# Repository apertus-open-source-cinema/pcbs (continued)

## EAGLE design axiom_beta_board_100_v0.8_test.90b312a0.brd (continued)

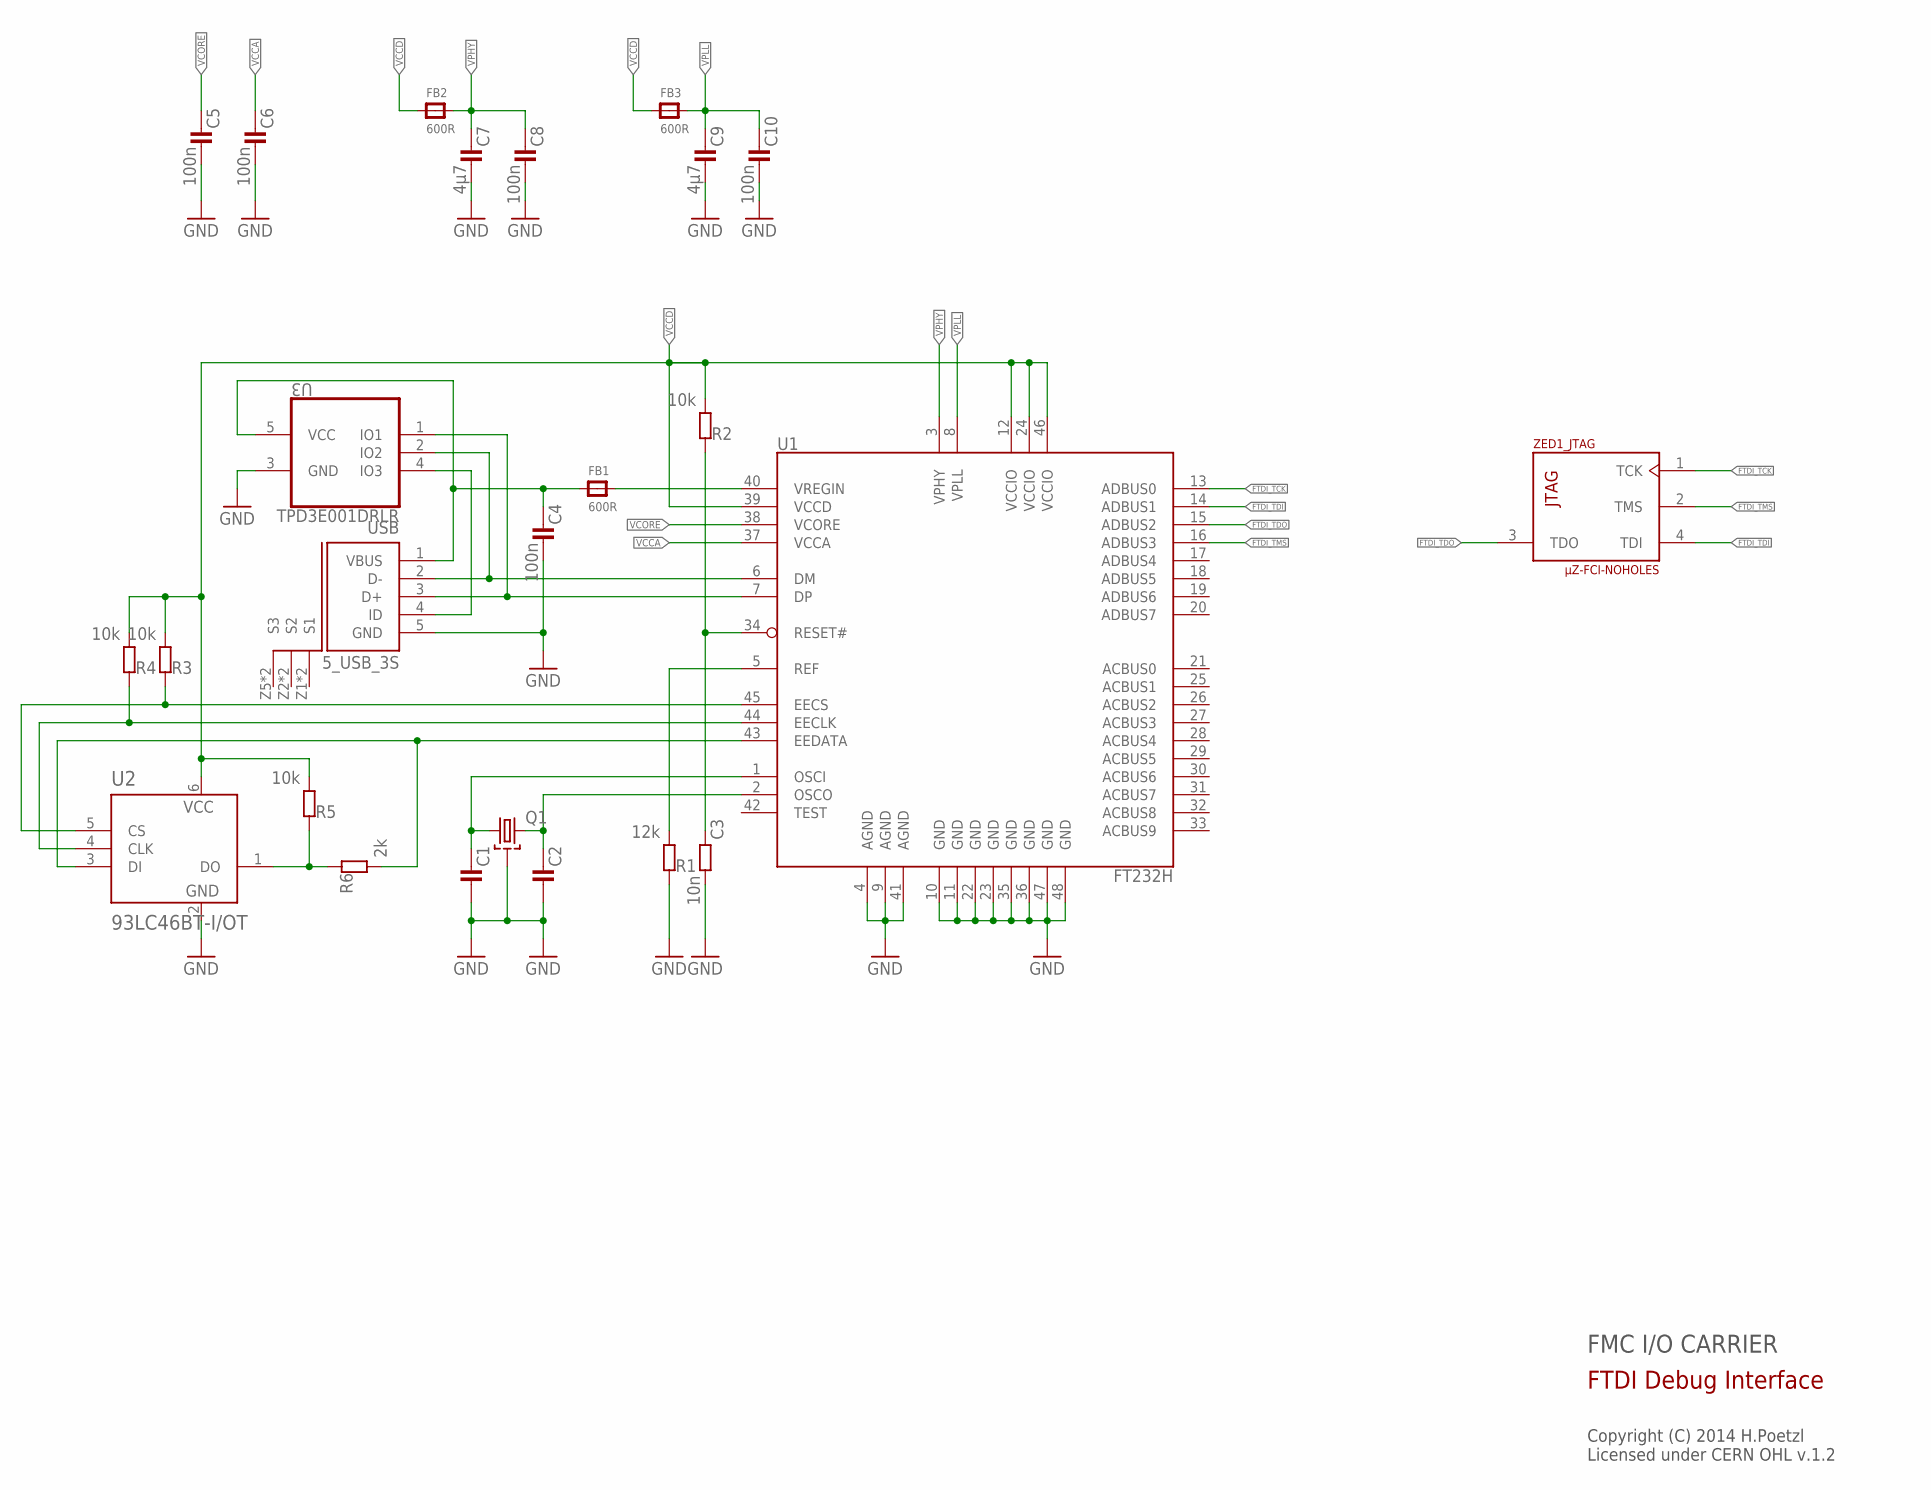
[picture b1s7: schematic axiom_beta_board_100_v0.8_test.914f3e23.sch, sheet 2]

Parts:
C1, C2: C0402-B; 0402-B
C3: 10n; 0402-B
C4: 100n; 0603-B
C5, C6, C8, C10: 100n; 0402-B
C7, C9: 4µ7; 0603-B
FB1, FB2, FB3: 600R; _0603MP
Q1: SMD-4P-2G-3.2X2.5; ABM8G
R1: 12k; 0402-B
R2, R3, R4, R5: 10k; 0402-B
R6: 2k; 0402-B
U1: FT232H; LQFP48
U2: 93LC46BT-I/OT; SOT95P280X145-6N
U3: TPD3E001DRLR; SOT50P160X60-5N
USB: 5_USB_3S; MICRO-AB-H-SMT
ZED1: µZ-FCI-NOHOLES; µZ-NOHOLES

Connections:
EE_CLK1: R4.1, U1.44 (EECLK), U2.4 (CLK)
EE_CS1: R3.1, U1.45 (EECS), U2.5 (CS)
EE_DATA1: R6.2, U1.43 (EEDATA), U2.3 (DI)
FTDI_D_N: U1.6 (DM), U3.2 (IO2), USB.2 (D-)
FTDI_D_P: U1.7 (DP), U3.1 (IO1), USB.3 (D+)
FTDI_TCK: U1.13 (ADBUS0), ZED1.1 (TCK)
FTDI_TDI: U1.14 (ADBUS1), ZED1.4 (TDI)
FTDI_TDO: U1.15 (ADBUS2), ZED1.3 (TDO)
FTDI_TMS: U1.16 (ADBUS3), ZED1.2 (TMS)
unnamed: R5.1, R6.1, U2.1 (DO)
unnamed: C1.1, Q1.1, U1.1 (OSCI)
unnamed: C2.1, Q1.3 (2), U1.2 (OSCO)
unnamed: C3.1, R2.1, U1.34 (RESET#)
unnamed: R1.2, U1.5 (REF)
unnamed: U3.4 (IO3), USB.4 (ID)
VBUS: C4.1, FB1.1, U3.5 (VCC), USB.1 (VBUS)
VCCA: C6.1, U1.37 (VCCA)
VCCD: FB2.1, FB3.1, R2.2, R3.2, R4.2, R5.2, U1.12 (VCCIO), U1.24 (VCCIO), U1.39 (VCCD), U1.46 (VCCIO), U2.6 (VCC)
VCORE: C5.1, U1.38 (VCORE)
VPHY: C7.1, C8.1, FB2.2, U1.3 (VPHY)
VPLL: C9.1, C10.1, FB3.2, U1.8 (VPLL)
VREGIN: FB1.2, U1.40 (VREGIN)

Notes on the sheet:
FMC I/O CARRIER
Copyright (C) 2014 H.Poetzl Licensed under CERN OHL v.1.2
FTDI Debug Interface

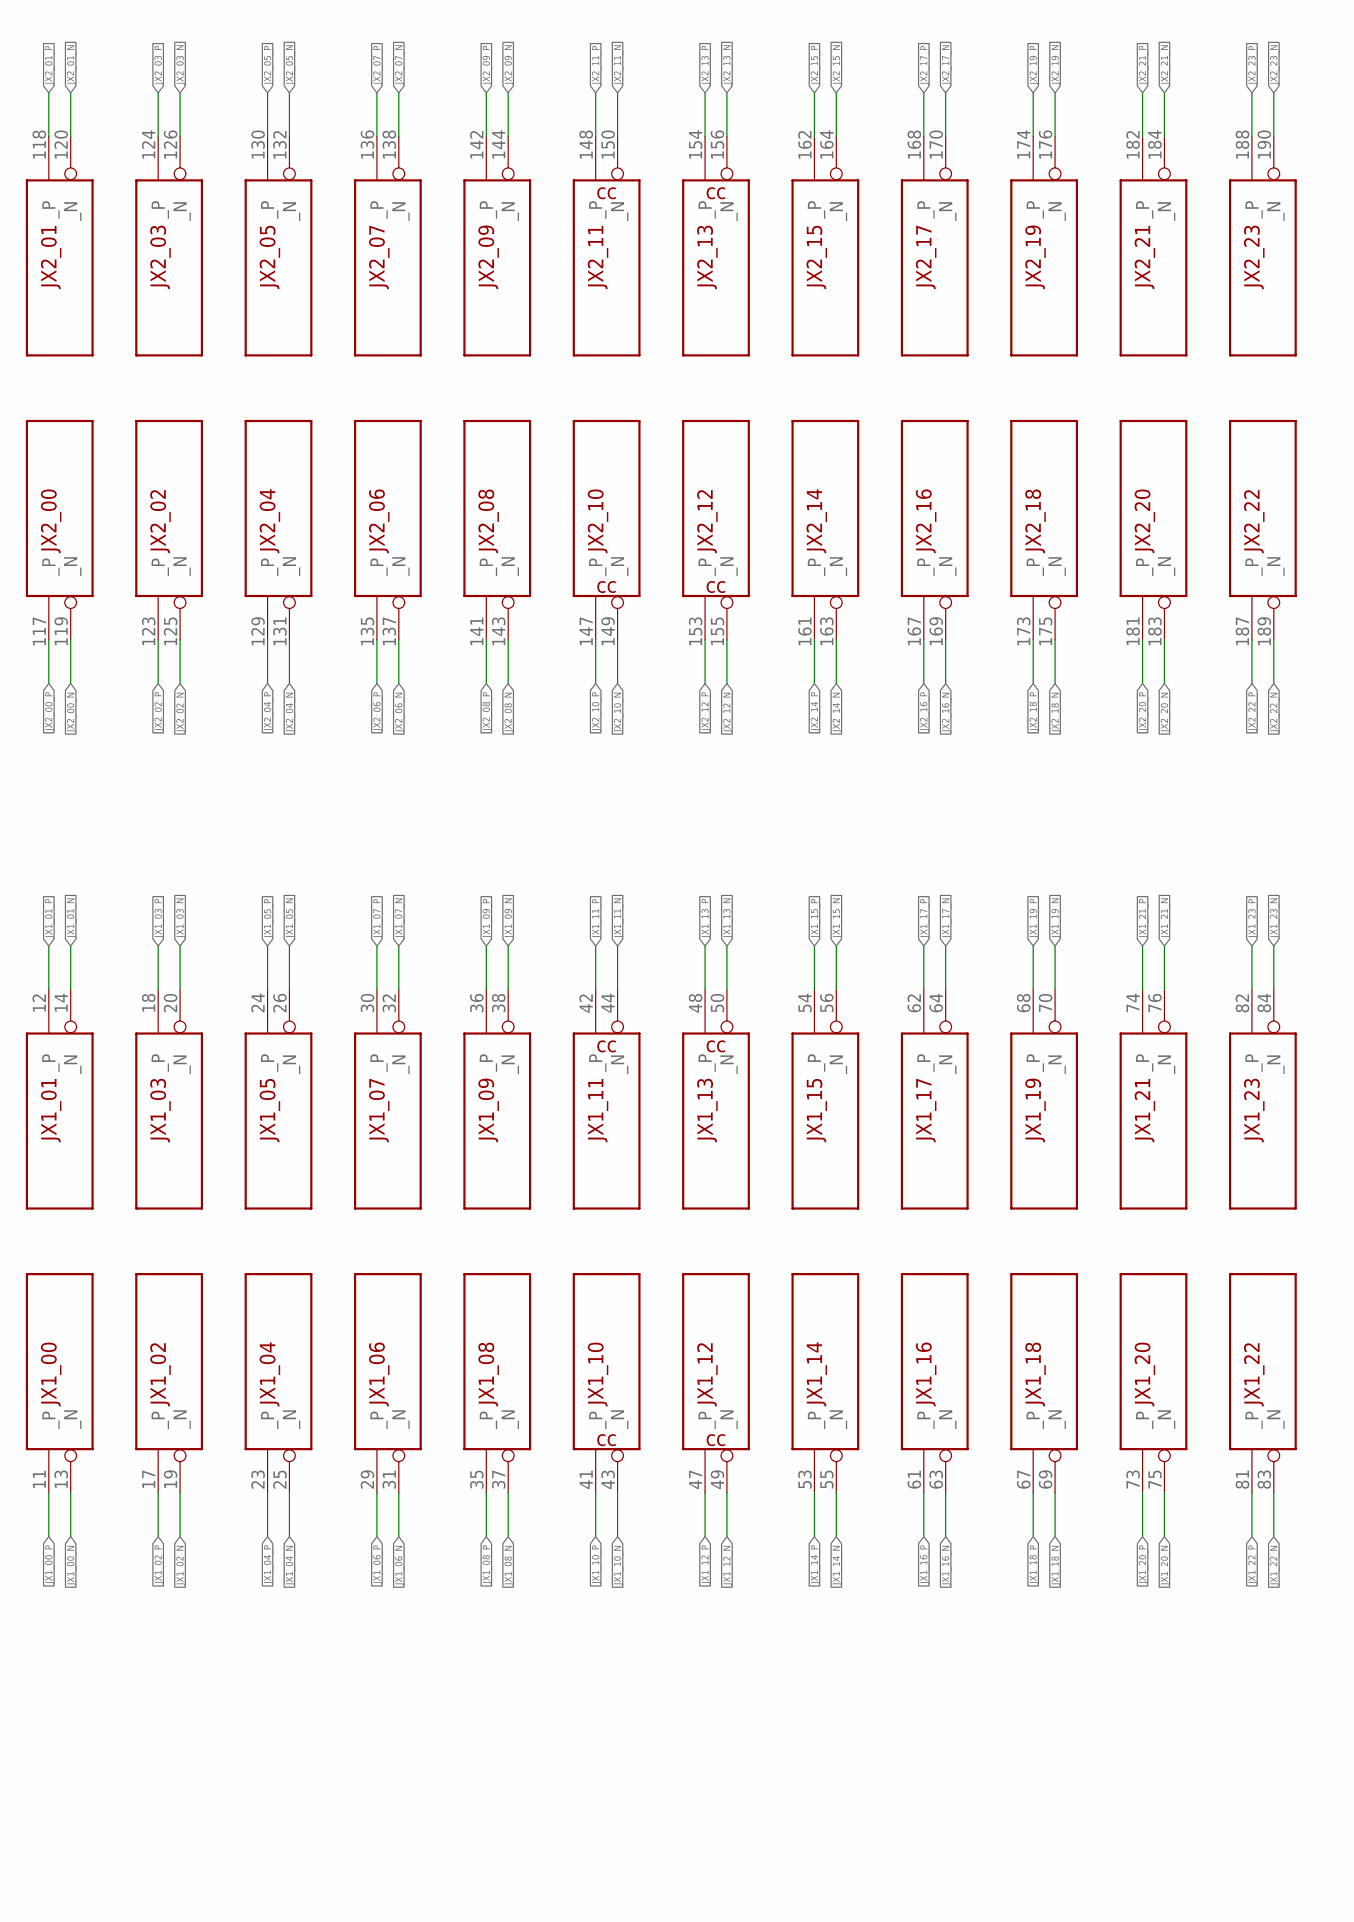
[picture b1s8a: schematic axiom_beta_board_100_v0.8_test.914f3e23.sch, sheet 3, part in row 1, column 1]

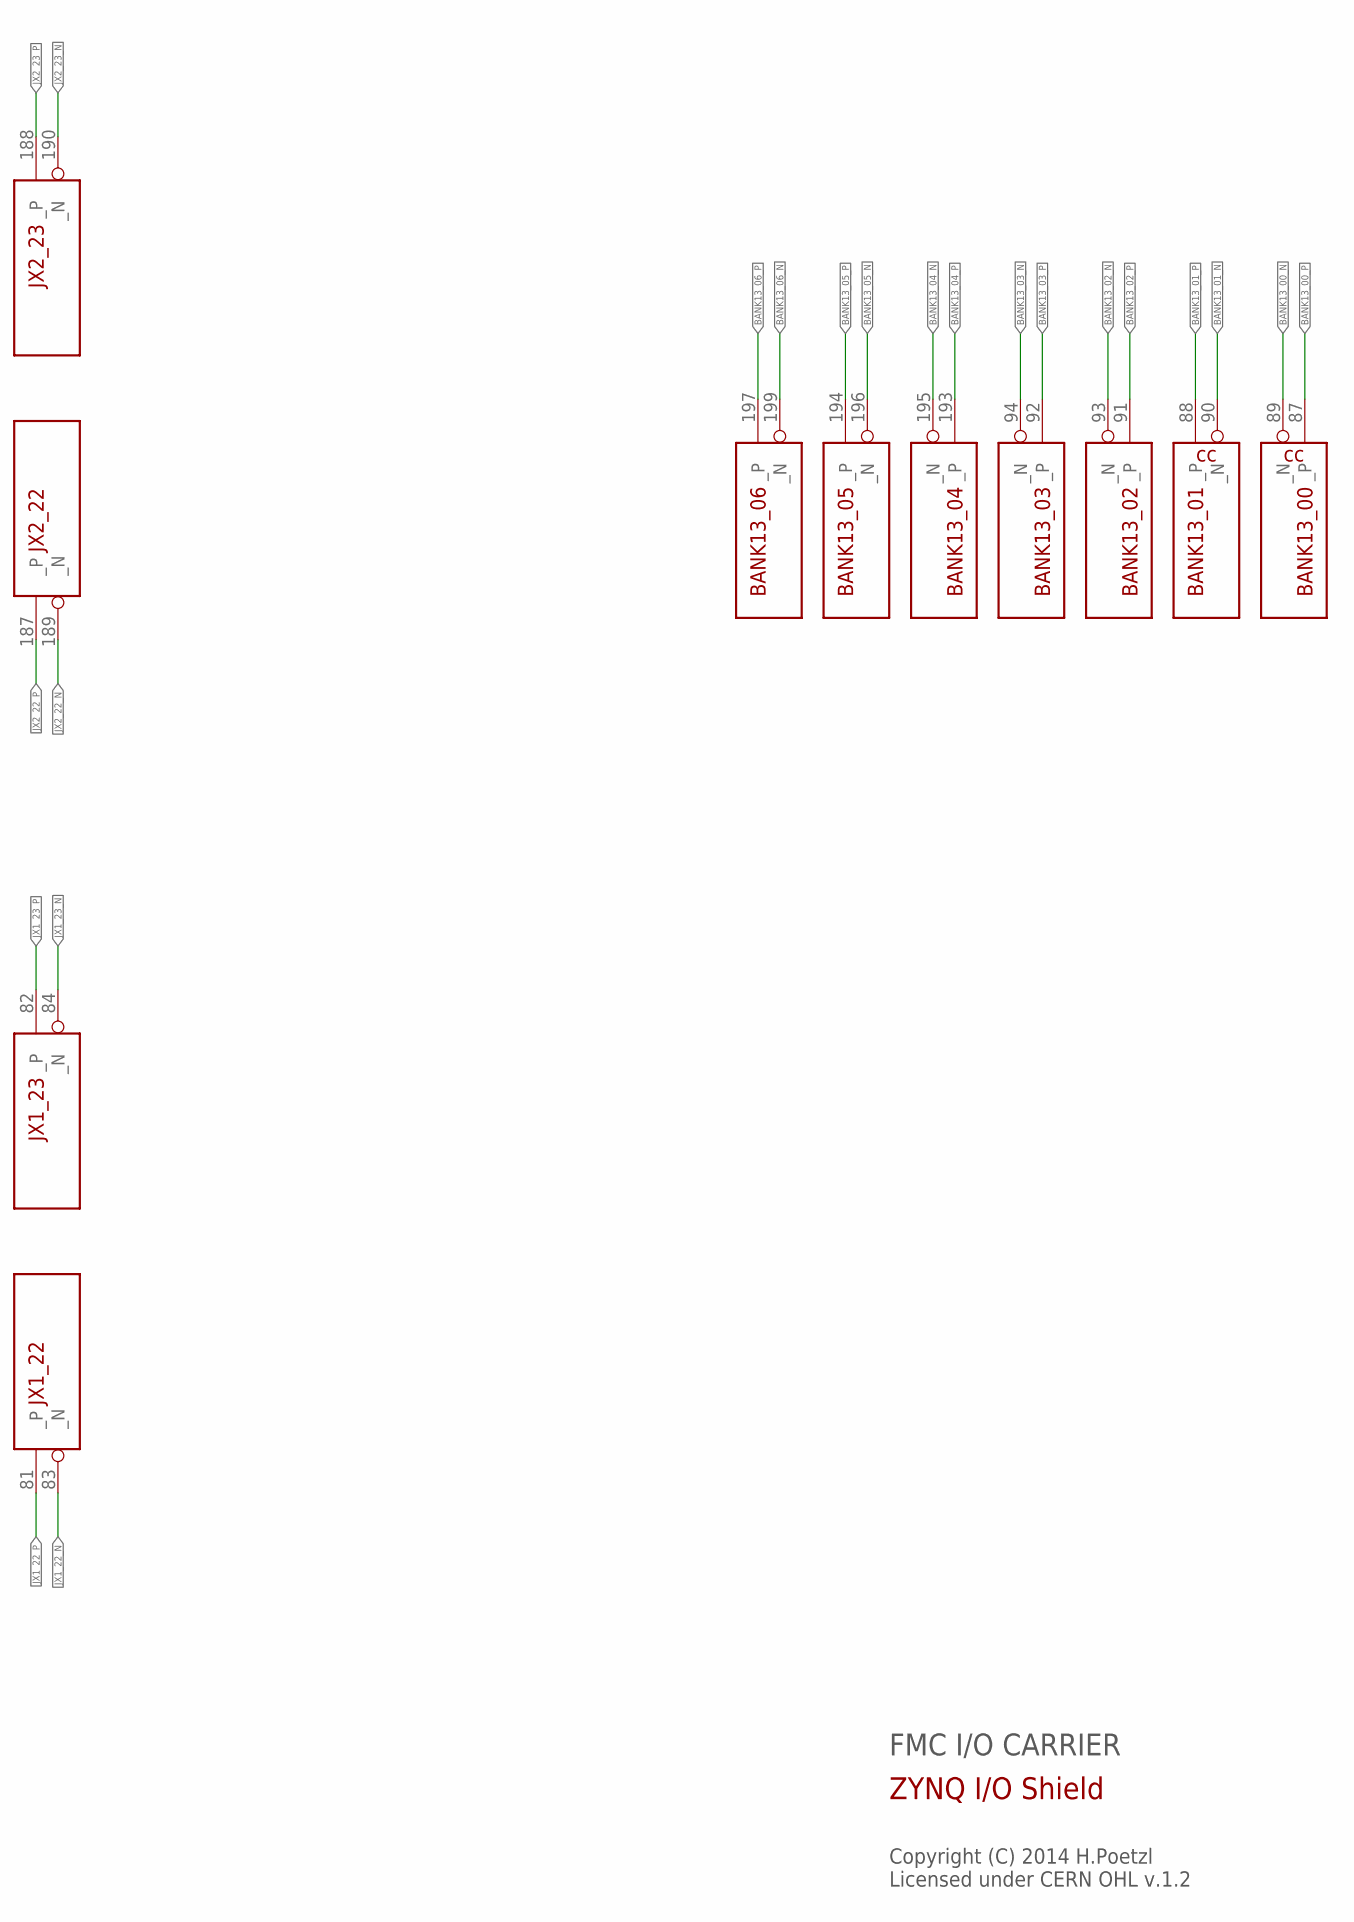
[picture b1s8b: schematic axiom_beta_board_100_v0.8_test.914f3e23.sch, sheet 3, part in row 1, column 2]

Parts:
ZED1: µZ-FCI-NOHOLES; µZ-NOHOLES

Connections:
BANK13_00_N: ZED1.89 (_N); also elsewhere on the board
BANK13_00_P: ZED1.87 (_P); also elsewhere on the board
BANK13_01_N: ZED1.90 (_N); also elsewhere on the board
BANK13_01_P: ZED1.88 (_P); also elsewhere on the board
BANK13_02_N: ZED1.93 (_N); also elsewhere on the board
BANK13_02_P: ZED1.91 (_P); also elsewhere on the board
BANK13_03_N: ZED1.94 (_N)
BANK13_03_P: ZED1.92 (_P)
BANK13_04_N: ZED1.195 (_N); also elsewhere on the board
BANK13_04_P: ZED1.193 (_P); also elsewhere on the board
BANK13_05_N: ZED1.196 (_N); also elsewhere on the board
BANK13_05_P: ZED1.194 (_P); also elsewhere on the board
BANK13_06_N: ZED1.199 (_N); also elsewhere on the board
BANK13_06_P: ZED1.197 (_P); also elsewhere on the board
JX1_00_N: ZED1.13 (_N); also elsewhere on the board
JX1_00_P: ZED1.11 (_P); also elsewhere on the board
JX1_01_N: ZED1.14 (_N); also elsewhere on the board
JX1_01_P: ZED1.12 (_P); also elsewhere on the board
JX1_02_N: ZED1.19 (_N); also elsewhere on the board
JX1_02_P: ZED1.17 (_P); also elsewhere on the board
JX1_03_N: ZED1.20 (_N); also elsewhere on the board
JX1_03_P: ZED1.18 (_P); also elsewhere on the board
JX1_04_N: ZED1.25 (_N); also elsewhere on the board
JX1_04_P: ZED1.23 (_P); also elsewhere on the board
JX1_05_N: ZED1.26 (_N); also elsewhere on the board
JX1_05_P: ZED1.24 (_P); also elsewhere on the board
JX1_06_N: ZED1.31 (_N); also elsewhere on the board
JX1_06_P: ZED1.29 (_P); also elsewhere on the board
JX1_07_N: ZED1.32 (_N); also elsewhere on the board
JX1_07_P: ZED1.30 (_P); also elsewhere on the board
JX1_08_N: ZED1.37 (_N); also elsewhere on the board
JX1_08_P: ZED1.35 (_P); also elsewhere on the board
JX1_09_N: ZED1.38 (_N); also elsewhere on the board
JX1_09_P: ZED1.36 (_P); also elsewhere on the board
JX1_10_N: ZED1.43 (_N); also elsewhere on the board
JX1_10_P: ZED1.41 (_P); also elsewhere on the board
JX1_11_N: ZED1.44 (_N); also elsewhere on the board
JX1_11_P: ZED1.42 (_P); also elsewhere on the board
JX1_12_N: ZED1.49 (_N); also elsewhere on the board
JX1_12_P: ZED1.47 (_P); also elsewhere on the board
JX1_13_N: ZED1.50 (_N); also elsewhere on the board
JX1_13_P: ZED1.48 (_P); also elsewhere on the board
JX1_14_N: ZED1.55 (_N); also elsewhere on the board
JX1_14_P: ZED1.53 (_P); also elsewhere on the board
JX1_15_N: ZED1.56 (_N); also elsewhere on the board
JX1_15_P: ZED1.54 (_P); also elsewhere on the board
JX1_16_N: ZED1.63 (_N); also elsewhere on the board
JX1_16_P: ZED1.61 (_P); also elsewhere on the board
JX1_17_N: ZED1.64 (_N); also elsewhere on the board
JX1_17_P: ZED1.62 (_P); also elsewhere on the board
JX1_18_N: ZED1.69 (_N); also elsewhere on the board
JX1_18_P: ZED1.67 (_P); also elsewhere on the board
JX1_19_N: ZED1.70 (_N); also elsewhere on the board
JX1_19_P: ZED1.68 (_P); also elsewhere on the board
JX1_20_N: ZED1.75 (_N); also elsewhere on the board
JX1_20_P: ZED1.73 (_P); also elsewhere on the board
JX1_21_N: ZED1.76 (_N); also elsewhere on the board
JX1_21_P: ZED1.74 (_P); also elsewhere on the board
JX1_22_N: ZED1.83 (_N); also elsewhere on the board
JX1_22_P: ZED1.81 (_P); also elsewhere on the board
JX1_23_N: ZED1.84 (_N); also elsewhere on the board
JX1_23_P: ZED1.82 (_P); also elsewhere on the board
JX2_00_N: ZED1.119 (_N); also elsewhere on the board
JX2_00_P: ZED1.117 (_P); also elsewhere on the board
JX2_01_N: ZED1.120 (_N); also elsewhere on the board
JX2_01_P: ZED1.118 (_P); also elsewhere on the board
JX2_02_N: ZED1.125 (_N); also elsewhere on the board
JX2_02_P: ZED1.123 (_P); also elsewhere on the board
JX2_03_N: ZED1.126 (_N); also elsewhere on the board
JX2_03_P: ZED1.124 (_P); also elsewhere on the board
JX2_04_N: ZED1.131 (_N); also elsewhere on the board
JX2_04_P: ZED1.129 (_P); also elsewhere on the board
JX2_05_N: ZED1.132 (_N); also elsewhere on the board
JX2_05_P: ZED1.130 (_P); also elsewhere on the board
JX2_06_N: ZED1.137 (_N); also elsewhere on the board
JX2_06_P: ZED1.135 (_P); also elsewhere on the board
JX2_07_N: ZED1.138 (_N); also elsewhere on the board
JX2_07_P: ZED1.136 (_P); also elsewhere on the board
JX2_08_N: ZED1.143 (_N); also elsewhere on the board
JX2_08_P: ZED1.141 (_P); also elsewhere on the board
JX2_09_N: ZED1.144 (_N); also elsewhere on the board
JX2_09_P: ZED1.142 (_P); also elsewhere on the board
JX2_10_N: ZED1.149 (_N); also elsewhere on the board
JX2_10_P: ZED1.147 (_P); also elsewhere on the board
JX2_11_N: ZED1.150 (_N); also elsewhere on the board
JX2_11_P: ZED1.148 (_P); also elsewhere on the board
JX2_12_N: ZED1.155 (_N); also elsewhere on the board
JX2_12_P: ZED1.153 (_P); also elsewhere on the board
JX2_13_N: ZED1.156 (_N); also elsewhere on the board
JX2_13_P: ZED1.154 (_P); also elsewhere on the board
JX2_14_N: ZED1.163 (_N); also elsewhere on the board
JX2_14_P: ZED1.161 (_P); also elsewhere on the board
JX2_15_N: ZED1.164 (_N); also elsewhere on the board
JX2_15_P: ZED1.162 (_P); also elsewhere on the board
JX2_16_N: ZED1.169 (_N); also elsewhere on the board
JX2_16_P: ZED1.167 (_P); also elsewhere on the board
JX2_17_N: ZED1.170 (_N); also elsewhere on the board
JX2_17_P: ZED1.168 (_P); also elsewhere on the board
JX2_18_N: ZED1.175 (_N); also elsewhere on the board
JX2_18_P: ZED1.173 (_P); also elsewhere on the board
JX2_19_N: ZED1.176 (_N); also elsewhere on the board
JX2_19_P: ZED1.174 (_P); also elsewhere on the board
JX2_20_N: ZED1.183 (_N); also elsewhere on the board
JX2_20_P: ZED1.181 (_P); also elsewhere on the board
JX2_21_N: ZED1.184 (_N); also elsewhere on the board
JX2_21_P: ZED1.182 (_P); also elsewhere on the board
JX2_22_N: ZED1.189 (_N); also elsewhere on the board
JX2_22_P: ZED1.187 (_P); also elsewhere on the board
JX2_23_N: ZED1.190 (_N); also elsewhere on the board
JX2_23_P: ZED1.188 (_P); also elsewhere on the board

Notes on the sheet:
FMC I/O CARRIER
Copyright (C) 2014 H.Poetzl Licensed under CERN OHL v.1.2
ZYNQ I/O Shield

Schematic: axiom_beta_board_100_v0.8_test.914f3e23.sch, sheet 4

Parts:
X-EAST: FX10-100/10S; FX10A-100S/10
X-WEST: FX10-100/10S; FX10A-100S/10

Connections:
E_EN: X-EAST.13; also elsewhere on the board
E_I2C_V: X-EAST.12, X-EAST.14; also elsewhere on the board
E_SCK: X-EAST.11; also elsewhere on the board
E_SCL: X-EAST.16; also elsewhere on the board
E_SDA: X-EAST.18; also elsewhere on the board
E_SDI: X-EAST.15; also elsewhere on the board
E_SDI_V: X-EAST.20, X-EAST.22; also elsewhere on the board
E_SDO: X-EAST.17; also elsewhere on the board
E_VE: X-EAST.80, X-EAST.82, X-EAST.83, X-EAST.84, X-EAST.85, X-EAST.87; also elsewhere on the board
E_VE_CV: X-EAST.89; also elsewhere on the board
E_VE_OV: X-EAST.94; also elsewhere on the board
E_VE_UV: X-EAST.92; also elsewhere on the board
JTAG_V: X-WEST.20, X-WEST.22; also elsewhere on the board
JX1_00_N: X-WEST.28; also elsewhere on the board
JX1_00_P: X-WEST.26; also elsewhere on the board
JX1_02_N: X-WEST.23; also elsewhere on the board
JX1_02_P: X-WEST.21; also elsewhere on the board
JX1_04_N: X-WEST.29; also elsewhere on the board
JX1_04_P: X-WEST.27; also elsewhere on the board
JX1_06_N: X-WEST.35; also elsewhere on the board
JX1_06_P: X-WEST.33; also elsewhere on the board
JX1_07_N: X-WEST.36; also elsewhere on the board
JX1_07_P: X-WEST.34; also elsewhere on the board
JX1_08_N: X-WEST.41; also elsewhere on the board
JX1_08_P: X-WEST.39; also elsewhere on the board
JX1_09_N: X-WEST.42; also elsewhere on the board
JX1_09_P: X-WEST.40; also elsewhere on the board
JX1_10_N: X-WEST.47; also elsewhere on the board
JX1_10_P: X-WEST.45; also elsewhere on the board
JX1_11_N: X-WEST.48; also elsewhere on the board
JX1_11_P: X-WEST.46; also elsewhere on the board
JX1_12_N: X-EAST.55; also elsewhere on the board
JX1_12_P: X-EAST.53; also elsewhere on the board
JX1_13_N: X-EAST.56; also elsewhere on the board
JX1_13_P: X-EAST.54; also elsewhere on the board
JX1_14_N: X-EAST.61; also elsewhere on the board
JX1_14_P: X-EAST.59; also elsewhere on the board
JX1_15_N: X-EAST.62; also elsewhere on the board
JX1_15_P: X-EAST.60; also elsewhere on the board
JX1_16_N: X-EAST.67; also elsewhere on the board
JX1_16_P: X-EAST.65; also elsewhere on the board
JX1_17_N: X-EAST.68; also elsewhere on the board
JX1_17_P: X-EAST.66; also elsewhere on the board
JX1_18_N: X-EAST.73; also elsewhere on the board
JX1_18_P: X-EAST.71; also elsewhere on the board
JX1_20_N: X-EAST.79; also elsewhere on the board
JX1_20_P: X-EAST.77; also elsewhere on the board
JX1_22_N: X-EAST.76; also elsewhere on the board
JX1_22_P: X-EAST.74; also elsewhere on the board
JX2_01_N: X-WEST.74; also elsewhere on the board
JX2_01_P: X-WEST.76; also elsewhere on the board
JX2_03_N: X-WEST.77; also elsewhere on the board
JX2_03_P: X-WEST.79; also elsewhere on the board
JX2_05_N: X-WEST.71; also elsewhere on the board
JX2_05_P: X-WEST.73; also elsewhere on the board
JX2_06_N: X-WEST.66; also elsewhere on the board
JX2_06_P: X-WEST.68; also elsewhere on the board
JX2_07_N: X-WEST.65; also elsewhere on the board
JX2_07_P: X-WEST.67; also elsewhere on the board
JX2_08_N: X-WEST.60; also elsewhere on the board
JX2_08_P: X-WEST.62; also elsewhere on the board
JX2_09_N: X-WEST.59; also elsewhere on the board
JX2_09_P: X-WEST.61; also elsewhere on the board
JX2_10_N: X-WEST.54; also elsewhere on the board
JX2_10_P: X-WEST.56; also elsewhere on the board
JX2_11_N: X-WEST.53; also elsewhere on the board
JX2_11_P: X-WEST.55; also elsewhere on the board
JX2_12_N: X-EAST.46; also elsewhere on the board
JX2_12_P: X-EAST.48; also elsewhere on the board
JX2_13_N: X-EAST.45; also elsewhere on the board
JX2_13_P: X-EAST.47; also elsewhere on the board
JX2_14_N: X-EAST.40; also elsewhere on the board
JX2_14_P: X-EAST.42; also elsewhere on the board
JX2_15_N: X-EAST.39; also elsewhere on the board
JX2_15_P: X-EAST.41; also elsewhere on the board
JX2_16_N: X-EAST.34; also elsewhere on the board
JX2_16_P: X-EAST.36; also elsewhere on the board
JX2_17_N: X-EAST.33; also elsewhere on the board
JX2_17_P: X-EAST.35; also elsewhere on the board
JX2_19_N: X-EAST.27; also elsewhere on the board
JX2_19_P: X-EAST.29; also elsewhere on the board
JX2_21_N: X-EAST.21; also elsewhere on the board
JX2_21_P: X-EAST.23; also elsewhere on the board
JX2_23_N: X-EAST.26; also elsewhere on the board
JX2_23_P: X-EAST.28; also elsewhere on the board
N_CHK_V: X-WEST.91, X-WEST.93; also elsewhere on the board
N_I2C_V: X-EAST.8, X-EAST.10; also elsewhere on the board
N_SCK: X-EAST.1; also elsewhere on the board
N_SCL: X-EAST.2; also elsewhere on the board
N_SDA: X-EAST.4; also elsewhere on the board
N_SDI: X-EAST.5; also elsewhere on the board
N_SDO: X-EAST.3; also elsewhere on the board
N_SPI_V: X-EAST.7, X-EAST.9; also elsewhere on the board
N_VE_CV: X-WEST.95; also elsewhere on the board
N_VE_OV: X-WEST.96; also elsewhere on the board
N_VE_UV: X-WEST.86; also elsewhere on the board
N_VN_CV: X-WEST.97; also elsewhere on the board
N_VN_OV: X-WEST.98; also elsewhere on the board
N_VN_UV: X-WEST.88; also elsewhere on the board
N_VW_CV: X-WEST.99; also elsewhere on the board
N_VW_OV: X-WEST.100; also elsewhere on the board
N_VW_UV: X-WEST.90; also elsewhere on the board
S_CHK_V: X-EAST.91, X-EAST.93; also elsewhere on the board
S_I2C_V: X-WEST.8, X-WEST.10; also elsewhere on the board
S_SCK: X-WEST.1; also elsewhere on the board
S_SCL: X-WEST.2; also elsewhere on the board
S_SDA: X-WEST.4; also elsewhere on the board
S_SDI: X-WEST.5; also elsewhere on the board
S_SDO: X-WEST.3; also elsewhere on the board
S_SPI_V: X-WEST.7, X-WEST.9; also elsewhere on the board
S_VE_CV: X-EAST.99; also elsewhere on the board
S_VE_OV: X-EAST.100; also elsewhere on the board
S_VE_UV: X-EAST.90; also elsewhere on the board
S_VS_CV: X-EAST.97; also elsewhere on the board
S_VS_OV: X-EAST.98; also elsewhere on the board
S_VS_UV: X-EAST.88; also elsewhere on the board
S_VW_CV: X-EAST.95; also elsewhere on the board
S_VW_OV: X-EAST.96; also elsewhere on the board
S_VW_UV: X-EAST.86; also elsewhere on the board
TCK: X-WEST.11; also elsewhere on the board
TDI: X-WEST.15; also elsewhere on the board
TDO: X-WEST.17; also elsewhere on the board
TMS: X-WEST.13; also elsewhere on the board
W_I2C_V: X-WEST.12, X-WEST.14; also elsewhere on the board
W_SCL: X-WEST.16; also elsewhere on the board
W_SDA: X-WEST.18; also elsewhere on the board
W_VW: X-WEST.80, X-WEST.82, X-WEST.83, X-WEST.84, X-WEST.85, X-WEST.87; also elsewhere on the board
W_VW_CV: X-WEST.89; also elsewhere on the board
W_VW_OV: X-WEST.94; also elsewhere on the board
W_VW_UV: X-WEST.92; also elsewhere on the board

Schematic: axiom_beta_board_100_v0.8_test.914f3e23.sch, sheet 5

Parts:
C11, C12, C13, C14, C15, C16, C17, C18: C1206-B; 1206-B
FPC-N: SFV24R-2STE1LF; FCI_SFV24R-2STE1LF
FPC-S: SFV24R-2STE1LF; FCI_SFV24R-2STE1LF
JP5, JP7: PINHD-2X08_2.54; 2X08
JP6, JP8: PINHD-2X06_2.54; 2X06
JP9: PINHD-1X02_2.54; 1X02
LED1, LED2, LED3, LED4, LED5, LED6, LED7, LED8, LED9, LED10, LED11, LED12: LEDCHIPLED_0603; CHIPLED_0603
PAD1, PAD2, PAD3, PAD4, PAD5, PAD6, PAD7, PAD8, PAD9, PAD10, PAD11, PAD12: SMD-PAD1.6X3.8MM-U; 1.6X3.8U-MM
PH-N: JST_5PIN; JST-PH-5-SMT-RA
PH-S: JST_5PIN; JST-PH-5-SMT-RA
RN1, RN2, RN3: 4R-NCAY16; CAY16

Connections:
BANK13_00_N: RN3.6 (2); also elsewhere on the board
BANK13_00_P: RN3.5 (2); also elsewhere on the board
BANK13_01_N: LED7.A, PAD10.1; also elsewhere on the board
BANK13_01_P: LED5.A, PAD9.1; also elsewhere on the board
BANK13_02_N: RN3.8 (2); also elsewhere on the board
BANK13_02_P: RN3.7 (2); also elsewhere on the board
BANK13_04_N: LED6.A, PAD3.1; also elsewhere on the board
BANK13_04_P: LED8.A, PAD4.1; also elsewhere on the board
BANK13_05_N: LED2.A, PAD1.1; also elsewhere on the board
BANK13_05_P: LED4.A, PAD2.1; also elsewhere on the board
BANK13_06_N: LED1.A, PAD7.1; also elsewhere on the board
BANK13_06_P: LED3.A, PAD8.1; also elsewhere on the board
E_EN: JP7.7; also elsewhere on the board
E_I2C_V: JP7.8; also elsewhere on the board
E_SCK: JP7.9; also elsewhere on the board
E_SCL: JP7.6; also elsewhere on the board
E_SDA: JP7.4; also elsewhere on the board
E_SDI: JP7.5; also elsewhere on the board
E_SDI_V: JP7.2; also elsewhere on the board
E_SDO: JP7.3; also elsewhere on the board
E_VE: C15.1, PH-S.5; also elsewhere on the board
E_VE_CV: FPC-S.17; also elsewhere on the board
E_VE_OV: FPC-S.6; also elsewhere on the board
E_VE_UV: FPC-S.7; also elsewhere on the board
JTAG_V: JP5.2; also elsewhere on the board
JX1_01_N: JP6.12; also elsewhere on the board
JX1_01_P: JP6.11; also elsewhere on the board
JX1_03_N: JP6.10; also elsewhere on the board
JX1_03_P: JP6.9; also elsewhere on the board
JX1_05_N: JP6.8; also elsewhere on the board
JX1_05_P: JP6.7; also elsewhere on the board
JX1_19_N: JP8.6; also elsewhere on the board
JX1_19_P: JP8.5; also elsewhere on the board
JX1_21_N: JP8.4; also elsewhere on the board
JX1_21_P: JP8.3; also elsewhere on the board
JX1_23_N: JP8.2; also elsewhere on the board
JX1_23_P: JP8.1; also elsewhere on the board
JX2_00_N: JP6.1; also elsewhere on the board
JX2_00_P: JP6.2; also elsewhere on the board
JX2_02_N: JP6.3; also elsewhere on the board
JX2_02_P: JP6.4; also elsewhere on the board
JX2_04_N: JP6.5; also elsewhere on the board
JX2_04_P: JP6.6; also elsewhere on the board
JX2_18_N: JP8.7; also elsewhere on the board
JX2_18_P: JP8.8; also elsewhere on the board
JX2_20_N: JP8.9; also elsewhere on the board
JX2_20_P: JP8.10; also elsewhere on the board
JX2_22_N: JP8.11; also elsewhere on the board
JX2_22_P: JP8.12; also elsewhere on the board
unnamed: LED1.C, RN1.8 (2)
unnamed: LED2.C, RN1.7 (2)
unnamed: LED3.C, RN1.6 (2)
unnamed: LED4.C, RN1.5 (2)
unnamed: LED5.C, RN2.8 (2)
unnamed: LED6.C, RN2.7 (2)
unnamed: LED7.C, RN2.6 (2)
unnamed: LED8.C, RN2.5 (2)
unnamed: LED9.A, RN3.1
unnamed: LED10.A, RN3.2 (1)
unnamed: LED11.A, RN3.3 (1)
unnamed: LED12.A, RN3.4 (1)
N_CHK_V: FPC-N.19, FPC-N.21, FPC-N.23; also elsewhere on the board
N_I2C_V: JP7.10; also elsewhere on the board
N_SCK: JP7.15; also elsewhere on the board
N_SCL: JP7.14; also elsewhere on the board
N_SDA: JP7.12; also elsewhere on the board
N_SDI: JP7.11; also elsewhere on the board
N_SDO: JP7.13; also elsewhere on the board
N_SPI_V: JP7.16; also elsewhere on the board
N_VE_CV: FPC-N.15; also elsewhere on the board
N_VE_OV: FPC-N.4; also elsewhere on the board
N_VE_UV: FPC-N.11; also elsewhere on the board
N_VN_CV: FPC-N.14; also elsewhere on the board
N_VN_OV: FPC-N.3; also elsewhere on the board
N_VN_UV: FPC-N.10; also elsewhere on the board
N_VW_CV: FPC-N.13; also elsewhere on the board
N_VW_OV: FPC-N.2; also elsewhere on the board
N_VW_UV: FPC-N.9; also elsewhere on the board
PMOD_VCC: JP9.1, PAD6.1, PAD12.1
S_CHK_V: FPC-S.19, FPC-S.21, FPC-S.23; also elsewhere on the board
S_I2C_V: JP5.10; also elsewhere on the board
S_SCK: JP5.15; also elsewhere on the board
S_SCL: JP5.14; also elsewhere on the board
S_SDA: JP5.12; also elsewhere on the board
S_SDI: JP5.11; also elsewhere on the board
S_SDO: JP5.13; also elsewhere on the board
S_SPI_V: JP5.16; also elsewhere on the board
S_VE_CV: FPC-S.13; also elsewhere on the board
S_VE_OV: FPC-S.2; also elsewhere on the board
S_VE_UV: FPC-S.9; also elsewhere on the board
S_VS_CV: FPC-S.14; also elsewhere on the board
S_VS_OV: FPC-S.3; also elsewhere on the board
S_VS_UV: FPC-S.10; also elsewhere on the board
S_VW_CV: FPC-S.15; also elsewhere on the board
S_VW_OV: FPC-S.4; also elsewhere on the board
S_VW_UV: FPC-S.11; also elsewhere on the board
TCK: JP5.9; also elsewhere on the board
TDI: JP5.5; also elsewhere on the board
TDO: JP5.3; also elsewhere on the board
TMS: JP5.7; also elsewhere on the board
W_I2C_V: JP5.8; also elsewhere on the board
W_SCL: JP5.6; also elsewhere on the board
W_SDA: JP5.4; also elsewhere on the board
W_VW: C14.1, PH-N.5; also elsewhere on the board
W_VW_CV: FPC-N.17; also elsewhere on the board
W_VW_OV: FPC-N.6; also elsewhere on the board
W_VW_UV: FPC-N.7; also elsewhere on the board

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
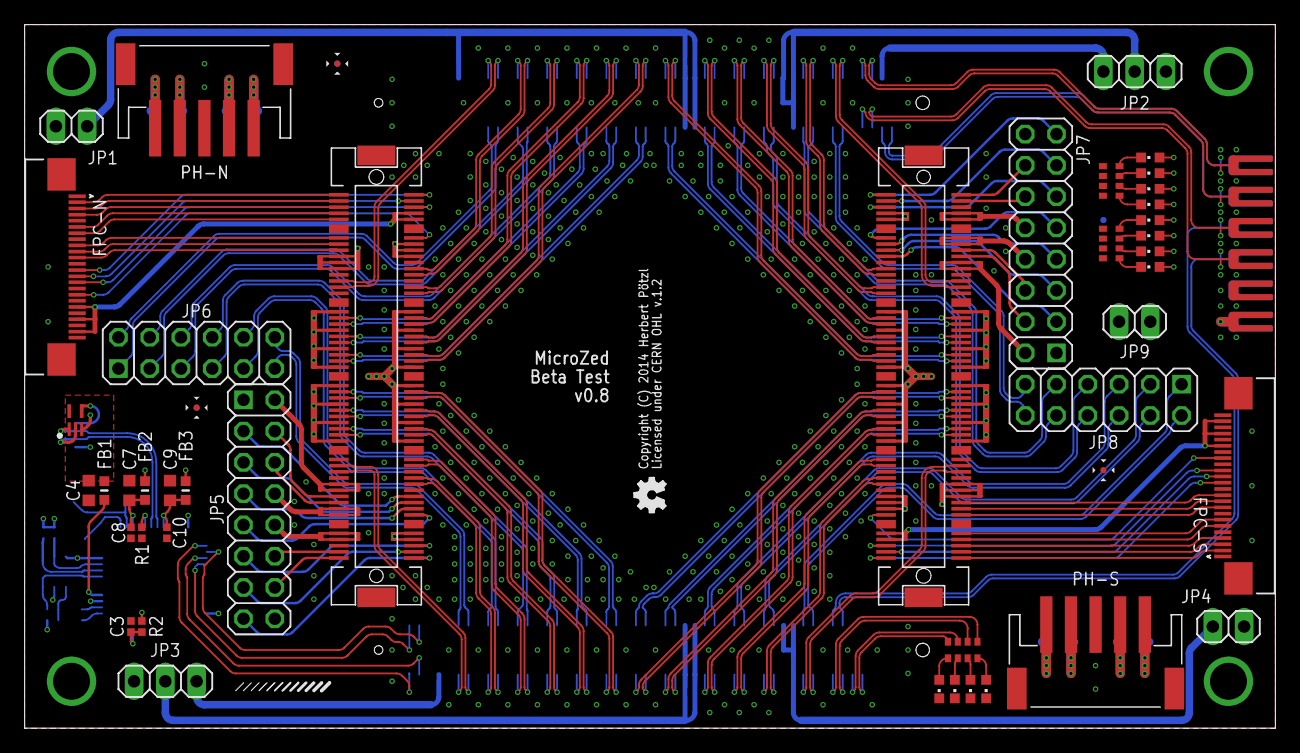
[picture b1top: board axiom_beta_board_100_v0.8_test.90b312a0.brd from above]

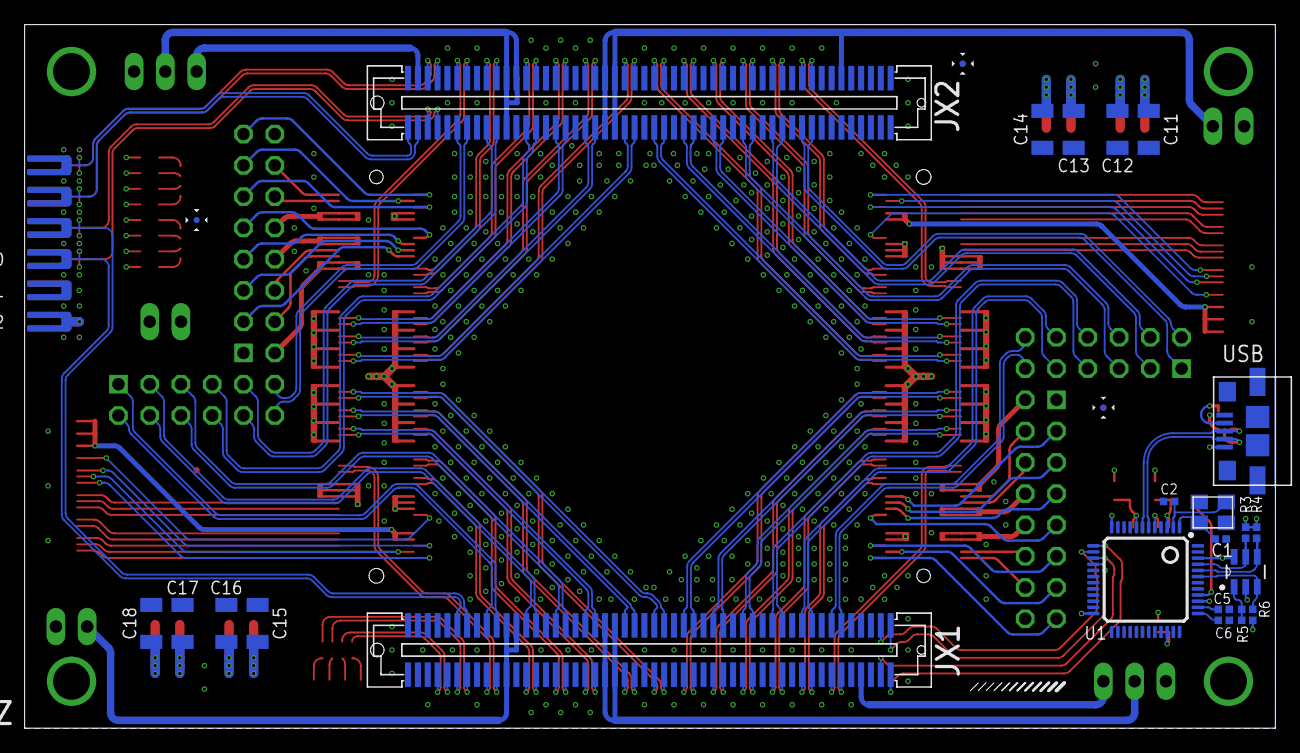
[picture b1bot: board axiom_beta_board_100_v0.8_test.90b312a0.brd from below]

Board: 4 copper layers, 101.6 x 57.1 mm, 76 parts (27 on the bottom side), 213 nets.

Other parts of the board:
LOGO1: OSHW_LOGO_FILLX0100-NT; OSHW_FILLX100_NOTEXT

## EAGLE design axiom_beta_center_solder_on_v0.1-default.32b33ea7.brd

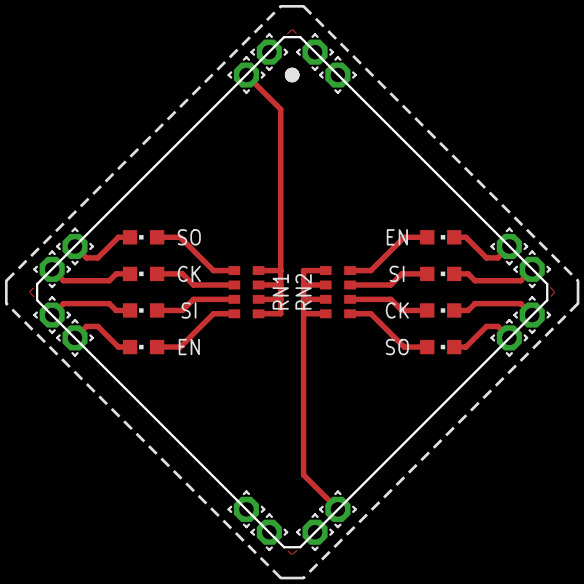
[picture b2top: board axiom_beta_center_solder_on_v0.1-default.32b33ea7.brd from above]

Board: 4 copper layers, 28.3 x 28.3 mm, 27 parts (1 on the bottom side), 19 nets.

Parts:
CK: CHIPLED_0603
EN: CHIPLED_0603
LED5, LED6, LED7, LED8: CHIPLED_0603
LOGO1: OSHW_LOGO_FILLX0100-NT; OSHW_FILLX100_NOTEXT
RN1, RN2: CAT16
SI: CHIPLED_0603
SO: CHIPLED_0603
U$1, U$2, U$3, U$4, U$5, U$6, U$11, U$14, U$15, U$16, U$17, U$18, U$19, U$20, U$21, U$22: PINPAD2.00MM; 1.4/0.8

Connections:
CSO_NW_V: RN1.5, RN1.6, RN1.7, RN1.8, U$18.1
CSO_SE_V: RN2.5, RN2.6, RN2.7, RN2.8, U$21.1
C_CK_E: LED6.C, U$14.1
C_CK_W: CK.C, U$1.1
C_EN_E: LED8.C, U$3.1
C_EN_W: EN.C, U$4.1
C_SI_E: LED7.C, U$15.1
C_SI_W: SI.C, U$2.1
C_SO_E: LED5.C, U$16.1
C_SO_W: SO.C, U$11.1
GND: U$5.1, U$6.1, U$17.1, U$20.1
unnamed: RN1.1, SO.A
unnamed: CK.A, RN1.2
unnamed: RN1.3, SI.A
unnamed: EN.A, RN1.4
unnamed: LED5.A, RN2.1
unnamed: LED6.A, RN2.2
unnamed: LED7.A, RN2.3
unnamed: LED8.A, RN2.4
